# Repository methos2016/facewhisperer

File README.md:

FaceWhisperer
-------------

FaceWhisperer is a hardware add-on for the [ChipWhisperer](https://newae.com/tools/chipwhisperer/) side-channel analysis tool, for working with devices that primarily communicate over USB. The goal is to create a USB host controller scripted with an experiment, all running totally synchronous with the target. This should give predictable timing each time the experiment is run from a target reset.

One proven use for this is to glitch GET_DESCRIPTOR requests into returning firmware images for devices that don't otherwise have firmware available for inspection.

The experiments are scripted from an ATxmega128 processor, same as the one included on ChipWhisperer-Lite. The USB host is a MAX3241E, inspired by Travis Goodspeed's [Facedancer21](http://goodfet.sourceforge.net/hardware/facedancer21/) tool.

For keeping the target device in sync, this board provides a 12 MHz clock output, an open-collector reset output, and a trigger input with adjustable voltage threshold.

This project is a quick hack that builds on the work and inspiration of several great projects:

- [GoodFET](http://goodfet.sourceforge.net)
- [ChipWhisperer](https://newae.com/tools/chipwhisperer)
- [Xmegaduino](https://github.com/Xmegaduino/Xmegaduino)
- [Arduino USB Host Shield library](https://github.com/felis/USB_Host_Shield_2.0)

Hardware Errata
---------------

The current PCB design is usable, but there are some changes that still need to be made before I'd recommend anyone manufacture the design:

- Labels on the silkscreen and copper layers. I was milling the Rev A board, so I kept it simple.
- The CLK output is rather weak. I used the NC7WZ14 because I had them on hand, but they're just barely up to the task.
- I originally included the second CLK SMA jack for clock glitching via the CWLite's crowbar FET, but that's silly and this should really just have an XOR on-board for inserting glitches in the target clock without disrupting the facewhisperer itself.
- The SYNCIN didn't make it into the first board design at all, I had to rework it on.
- I didn't include headers for the spare GPIOs in the first board, for expediency's sake, but these would be an obviously handy addition.
- Connector placement is awkward. Rethink this around optimal coax routing.
- FTDI header for sniffing the serial bus. Jumper for optional transmit. I ended up using an FTDI cable to log the results while also allowing CWLite's serial port to orchestrate the glitching process.
- Maybe use a better transistor for the reset puller. The 2N7000 was just what I had handy. Also maybe take the LED off the gate, it may have been causing some 100ns-scale glitches in the reset's falling edge.
- Lots more test points and posts and things for you to grab onto with a logic analyzer.

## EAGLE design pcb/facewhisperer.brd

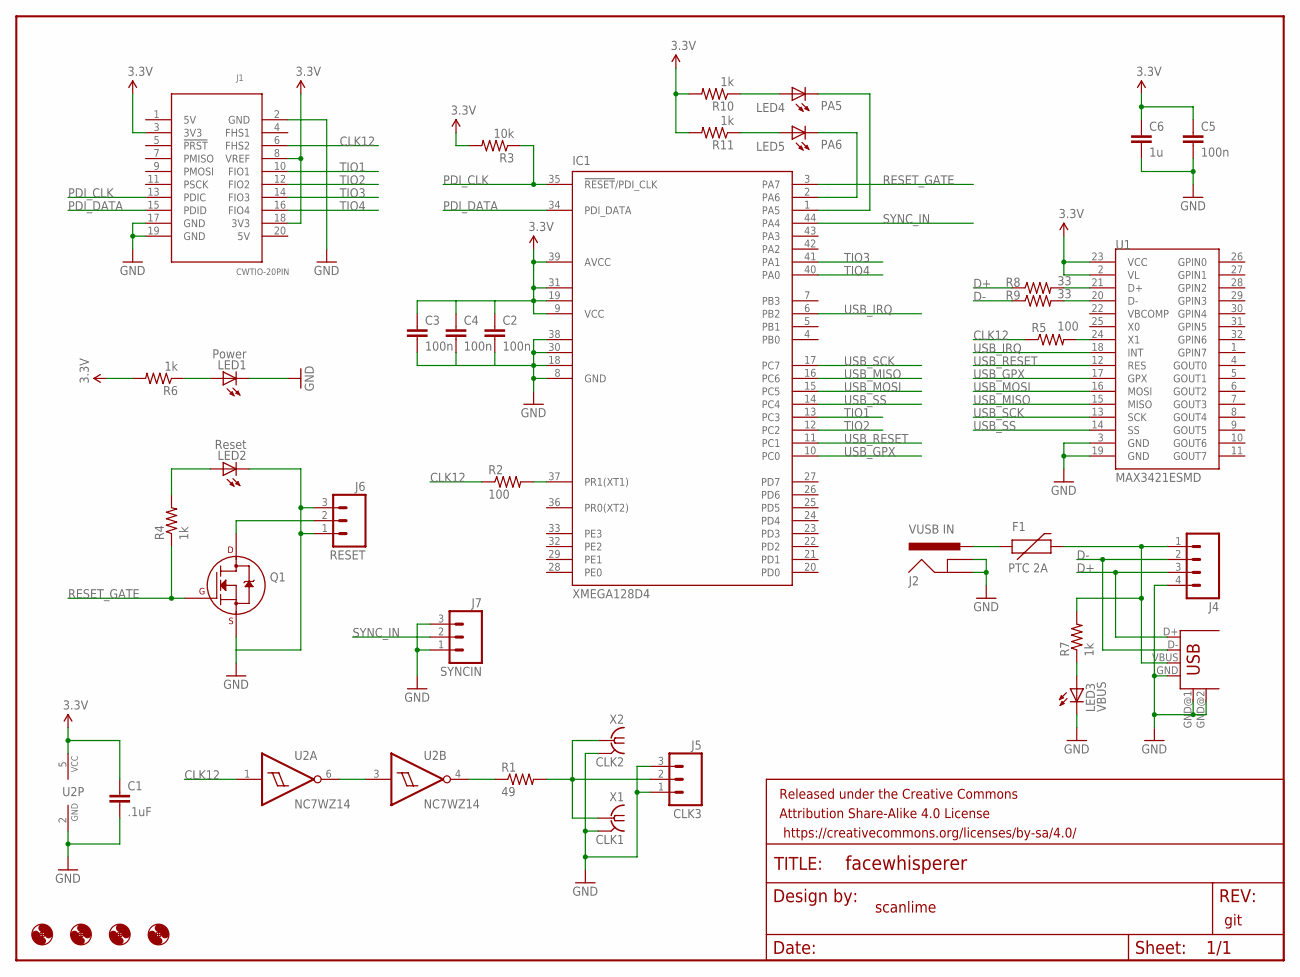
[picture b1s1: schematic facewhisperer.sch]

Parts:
C1: .1uF; 0805
C2, C3, C4, C5: 100n; 0805
C6: 1u; 0805
F1: PTC 2A; PTC-1206-WIDE
FRAME1: FRAME-LETTERNO_PACKAGE; DUMMY
H1, H2, H3, H4: MOUNT-HOLE3.2; 3,2
IC1: XMEGA128D4; TQFP44
J1: CWTIO-20PIN; PINSHRD_PTH_2X10
J2: VUSB IN; POWER_JACK_PTH
J3: USB-A-H
J4: M04LOCK_LONGPADS; 1X04_LOCK_LONGPADS
J5: CLK3; 1X03_LOCK_LONGPADS
J6: RESET; 1X03_LOCK_LONGPADS
J7: SYNCIN; 1X03_LOCK_LONGPADS
LED1: Power; 1206
LED2: Reset; 1206
LED3: VBUS; 1206
LED4: PA5; 1206
LED5: PA6; 1206
Q1: 2N7002_SOT23; SOT-23
R1: 49; 0805
R2, R5: 100; 0805
R3: 10k; 0805
R4, R6, R7, R10, R11: 1k; 0805
R8, R9: 33; 0805
U1: MAX3421ESMD; TQFP32-5MM-MILLABLE
U2: NC7WZ14; SC70-6-MILLABLE
X1: CLK1; J502-ND-142-0711-821/826-NOSILK
X2: CLK2; J502-ND-142-0711-821/826-NOSILK

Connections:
3.3V: C1.1, C2.1, C3.1, C4.1, C5.1, C6.1, IC1.9 (VCC), IC1.19 (VCC1), IC1.31 (VCC2), IC1.39 (AVCC), J1.3 (3V3), J1.8 (VREF), J1.18 (3V3), R3.2, R6.2, R10.2, R11.2, U1.2 (VL), U1.23 (VCC), U2.5 (VCC)
CLK12: J1.6 (FHS2), R2.1, R5.1, U2.1 (IN)
D+: J3.D+, J4.3, R8.1
D-: J3.D-, J4.2, R9.1
GND: C1.2, C2.2, C3.2, C4.2, C5.2, C6.2, IC1.8 (GND), IC1.18 (GND1), IC1.30 (GND2), IC1.38 (GND3), J1.2 (GND), J1.17 (GND), J1.19 (GND), J2.GND, J2.GNDBREAK, J3.GND, J3.GND@1 (GND), J3.GND@2 (GND), J4.4, J5.1, J5.3, J6.1, J6.3, J7.1, J7.3, LED1.C, LED2.C, LED3.C, Q1.2 (S), U1.3 (GND), U1.19 (GND), U2.2 (GND), X1.G@1 (2), X1.G@2 (2), X1.G@3 (2), X1.G@4 (2), X2.G@1 (2), X2.G@2 (2), X2.G@3 (2), X2.G@4 (2)
unnamed: U2.3 (IN), U2.6 (OUT)
unnamed: R1.1, U2.4 (OUT)
unnamed: J5.2, R1.2, X1.1, X2.1
unnamed: R5.2, U1.24 (X1)
unnamed: F1.2, J3.VBUS, J4.1, R7.2
unnamed: LED2.A, R4.2
unnamed: IC1.37 (PR1(XT1)), R2.2
unnamed: J6.2, Q1.3 (D)
unnamed: LED1.A, R6.1
unnamed: LED3.A, R7.1
unnamed: R9.2, U1.20 (D-)
unnamed: R8.2, U1.21 (D+)
unnamed: F1.1, J2.PWR
unnamed: LED4.A, R10.1
unnamed: LED5.A, R11.1
unnamed: IC1.2 (PA6), LED5.C
unnamed: IC1.1 (PA5), LED4.C
PDI_CLK: IC1.35 (!RESET!/PDI_CLK), J1.13 (PDIC), R3.1
PDI_DATA: IC1.34 (PDI_DATA), J1.15 (PDID)
RESET_GATE: IC1.3 (PA7), Q1.1 (G), R4.1
SYNC_IN: IC1.44 (PA4), J7.2
TIO1: IC1.13 (PC3), J1.10 (FIO1)
TIO2: IC1.12 (PC2), J1.12 (FIO2)
TIO3: IC1.41 (PA1), J1.14 (FIO3)
TIO4: IC1.40 (PA0), J1.16 (FIO4)
USB_GPX: IC1.10 (PC0), U1.17 (GPX)
USB_IRQ: IC1.6 (PB2), U1.18 (INT)
USB_MISO: IC1.16 (PC6), U1.15 (MISO)
USB_MOSI: IC1.15 (PC5), U1.16 (MOSI)
USB_RESET: IC1.11 (PC1), U1.12 (RES)
USB_SCK: IC1.17 (PC7), U1.13 (SCK)
USB_SS: IC1.14 (PC4), U1.14 (SS)

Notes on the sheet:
scanlime
git

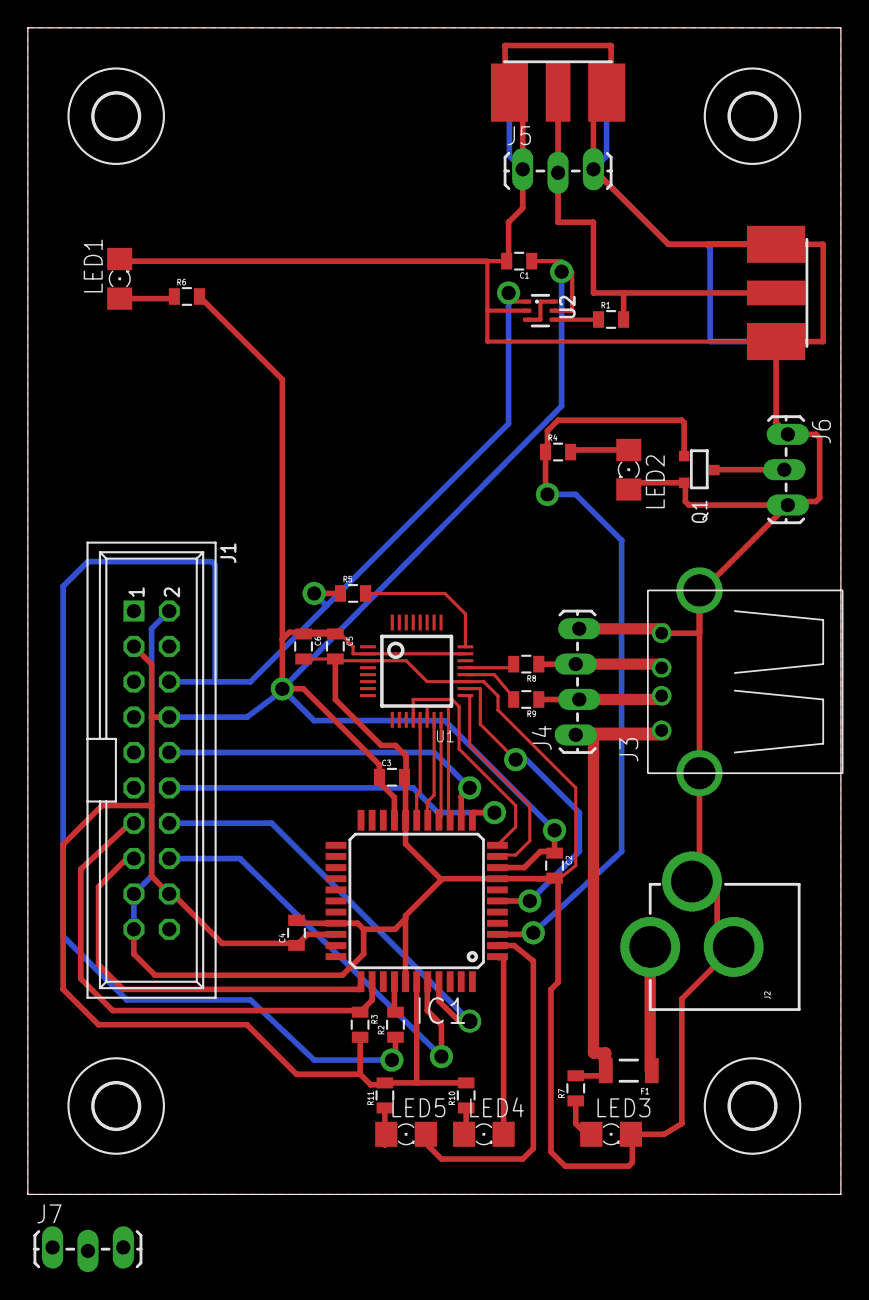
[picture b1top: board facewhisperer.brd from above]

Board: 2 copper layers, 58.4 x 83.8 mm, 41 parts (0 on the bottom side), 37 nets.

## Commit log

2016-09-01 Describe the project
2016-09-01 This will be open, but probably not MIT
    The hardware license is TBD; software is probably going to be GPL because it's based on the Arduino lib.
2016-09-01 Starting an Eagle design
2016-09-02 First rev of the PCB design
2016-09-02 Rev A
2016-09-02 Add a PDF schematic for Rev A
2016-09-02 Let's base the firmware on ChipWhisperer's framework
2016-09-02 Firmware build results
2016-09-02 Remove AVR support from this repo
2016-09-02 Local fork of the Arduino USB_Host_Shield_2.0
    Copied from:
    https://github.com/felis/USB_Host_Shield_2.0
    This is after one aborted attempt to make this build as a git submodule.
    For now, it seems better to hack this up locally and avoid pulling in
    much Arduino fluff.
2016-09-02 Build system updates for including USB
2016-09-02 Build fixes
2016-09-02 Include parts of Xmegaduino core
    Rather than gut the arduino support from the USB host library,
    I'm including a minimal subset of Xmegaduino so that the
    mods to usbhost can stay minimal.
2016-09-02 Initial changes to make usbhost compile
2016-09-02 Build fixes for Arduino-style serial port
2016-09-02 Basic ChipWhisperer GUI script for dev purposes
2016-09-02 Debugging
2016-09-03 Hardware bringup
2016-09-03 Init triggers automatically
2016-09-03 SPI fixes
2016-09-03 Make the usb-descriptor-simple example
2016-09-03 Reset USB and the local state each time
2016-09-03 Whitespace
2016-09-03 Decided against hex for now
2016-09-03 Add a sync input for use with analog comparator
2016-09-03 Update with SYNCIN port
2016-09-03 Sync notes
2016-09-03 Nice stable triggering
2016-09-03 Nitpicks
2016-09-03 Start stripping out unneeded and/or variable delays
2016-09-04 Non-RTC timer module with later synchronization
2016-09-04 Fix false sync while reset is still in progress
2016-09-04 Trigger later; not quite stable though
2016-09-04 Latest settings for homing in on GET_DESCRIPTOR
2016-09-04 Starting Glitch Explorer integration
2016-09-04 Starting to see get_descriptor glitches
2016-09-04 Looking for longer than usual responses
2016-09-05 Better response filter
2016-09-05 Semi-reliable glitch settings
2016-09-05 Faster serial
2016-09-05 New streaming IN to avoid filling up RAM
2016-09-05 Going long!
2016-09-05 Successfully extracted some firmware
2016-09-05 Write up hardware errata
    while it's still fresh in my mind

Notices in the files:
parts and their libraries:
SparkFun-DigitalIC: Licensing: Creative Commons ShareAlike 4.0 International - https://creativecommons.org/licenses/by-sa/4.0
fairchild-semi: Copyright (C) 2010, Bob Starr
SparkFun-Aesthetics: Released under the Creative Commons Attribution Share-Alike 4.0 License
